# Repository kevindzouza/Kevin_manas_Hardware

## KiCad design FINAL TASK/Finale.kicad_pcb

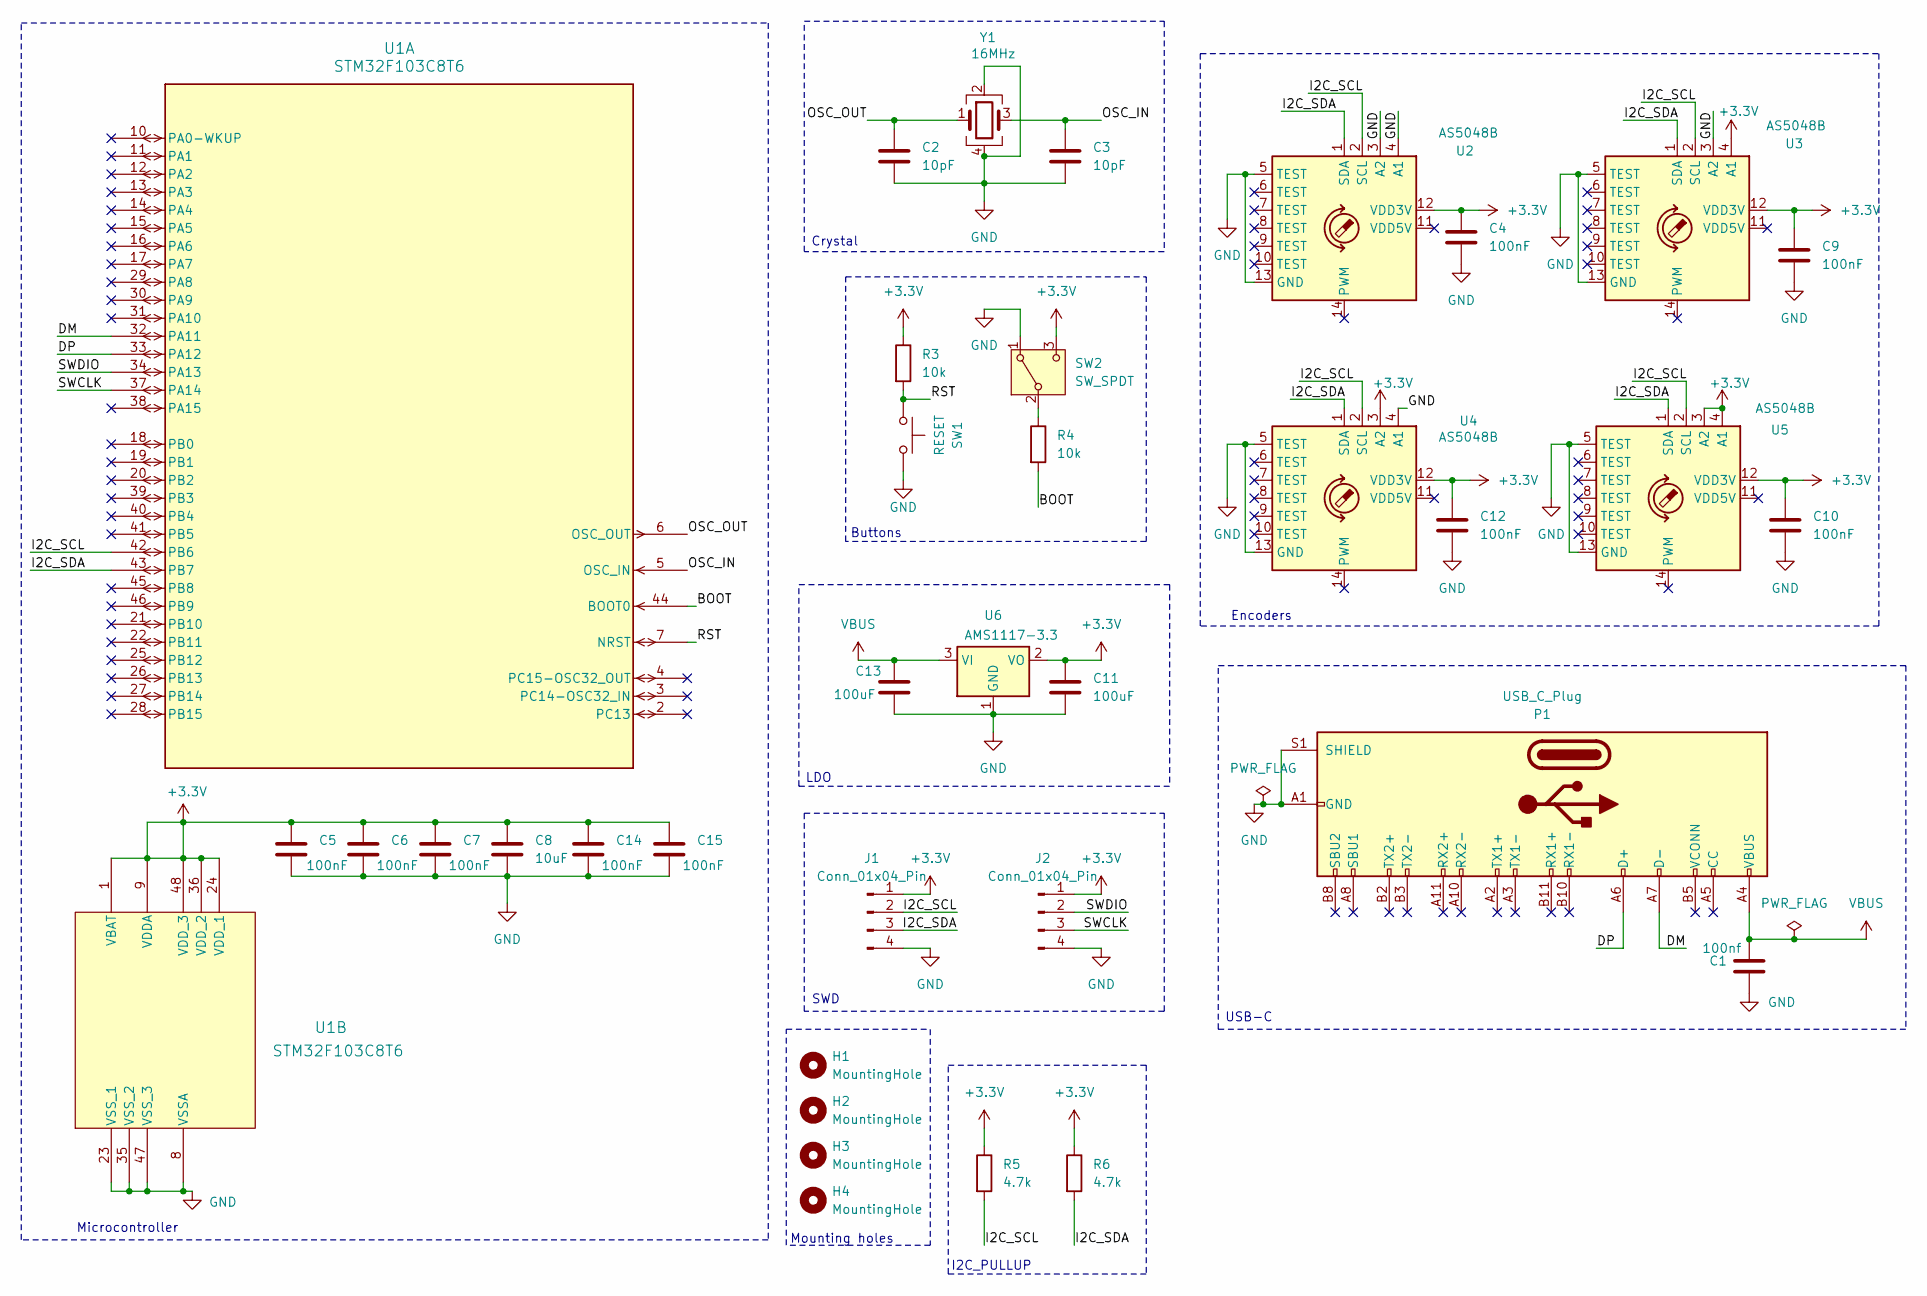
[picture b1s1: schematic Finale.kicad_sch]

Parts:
C1: 100nf; C_0805_2012Metric
C2, C3: 10pF; C_0402_1005Metric
C4, C5, C6, C7, C9, C10, C12, C14, C15: 100nF; C_0402_1005Metric
C8: 10uF; C_0805_2012Metric
C11, C13: 100uF; C_0402_1005Metric
H1, H2, H3, H4: MountingHole; MountingHole_2.1mm
J1, J2: Conn_01x04_Pin; JST_VH_B4P-VH-FB-B_1x04_P3.96mm_Vertical
P1: USB_C_Plug; GCT_USB4085-GF-A_REVB
R3, R4: 10k; R_0805_2012Metric
R5, R6: 4.7k; R_0805_2012Metric
SW1: RESET; SW_FSM8JH
SW2: SW_SPDT; SW_MINI-SPDT-SW
U1: STM32F103C8T6; LQFP48_STM
U2, U3, U4, U5: AS5048B; TSSOP-14_4.4x5mm_P0.65mm
U6: AMS1117-3.3; SOT-223-3_TabPin2
Y1: 16MHz; Crystal_SMD_3225-4Pin_3.2x2.5mm

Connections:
+3.3V: C4.1, C5.1, C6.1, C7.1, C8.1, C9.1, C10.1, C11.1, C12.1, C14.1, C15.1, J1.1, J2.1, R3.1, R5.1, R6.1, SW2.3 (C), U1.1 (VBAT), U1.9 (VDDA), U1.24 (VDD_1), U1.36 (VDD_2), U1.48 (VDD_3), U2.12 (VDD3V), U3.4 (A1), U3.12 (VDD3V), U4.3 (A2), U4.12 (VDD3V), U5.3 (A2), U5.4 (A1), U5.12 (VDD3V), U6.2 (VO)
/BOOT: R4.2, U1.44 (BOOT0)
/DM: P1.A7 (D-), U1.32 (PA11)
/DP: P1.A6 (D+), U1.33 (PA12)
/I2C_SCL: J1.2, R5.2, U1.42 (PB6), U2.2 (SCL), U3.2 (SCL), U4.2 (SCL), U5.2 (SCL)
/I2C_SDA: J1.3, R6.2, U1.43 (PB7), U2.1 (SDA), U3.1 (SDA), U4.1 (SDA), U5.1 (SDA)
/OSC_IN: C3.1, U1.5 (OSC_IN), Y1.3
/OSC_OUT: C2.1, U1.6 (OSC_OUT), Y1.1
/RST: R3.2, SW1.1, U1.7 (NRST)
/SWCLK: J2.3, U1.37 (PA14)
/SWDIO: J2.2, U1.34 (PA13)
GND: C1.1, C2.2, C3.2, C4.2, C5.2, C6.2, C7.2, C8.2, C9.2, C10.2, C11.2, C12.2, C13.2, C14.2, C15.2, J1.4, J2.4, P1.A1 (GND), P1.A12 (GND), P1.B1 (GND), P1.B12 (GND), P1.S1 (SHIELD), SW1.2, SW2.1 (A), U1.8 (VSSA), U1.23 (VSS_1), U1.35 (VSS_2), U1.47 (VSS_3), U2.3 (A2), U2.4 (A1), U2.5 (TEST), U2.13 (GND), U3.3 (A2), U3.5 (TEST), U3.13 (GND), U4.4 (A1), U4.5 (TEST), U4.13 (GND), U5.5 (TEST), U5.13 (GND), U6.1 (GND), Y1.2, Y1.4
unnamed: R4.1, SW2.2 (B)
VBUS: C1.2, C13.1, P1.A4 (VBUS), P1.A9 (VBUS), P1.B4 (VBUS), P1.B9 (VBUS), U6.3 (VI)

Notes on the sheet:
SWD
LDO
Encoders
USB-C
Microcontroller
Mounting holes
Buttons
I2C_PULLUP
Crystal

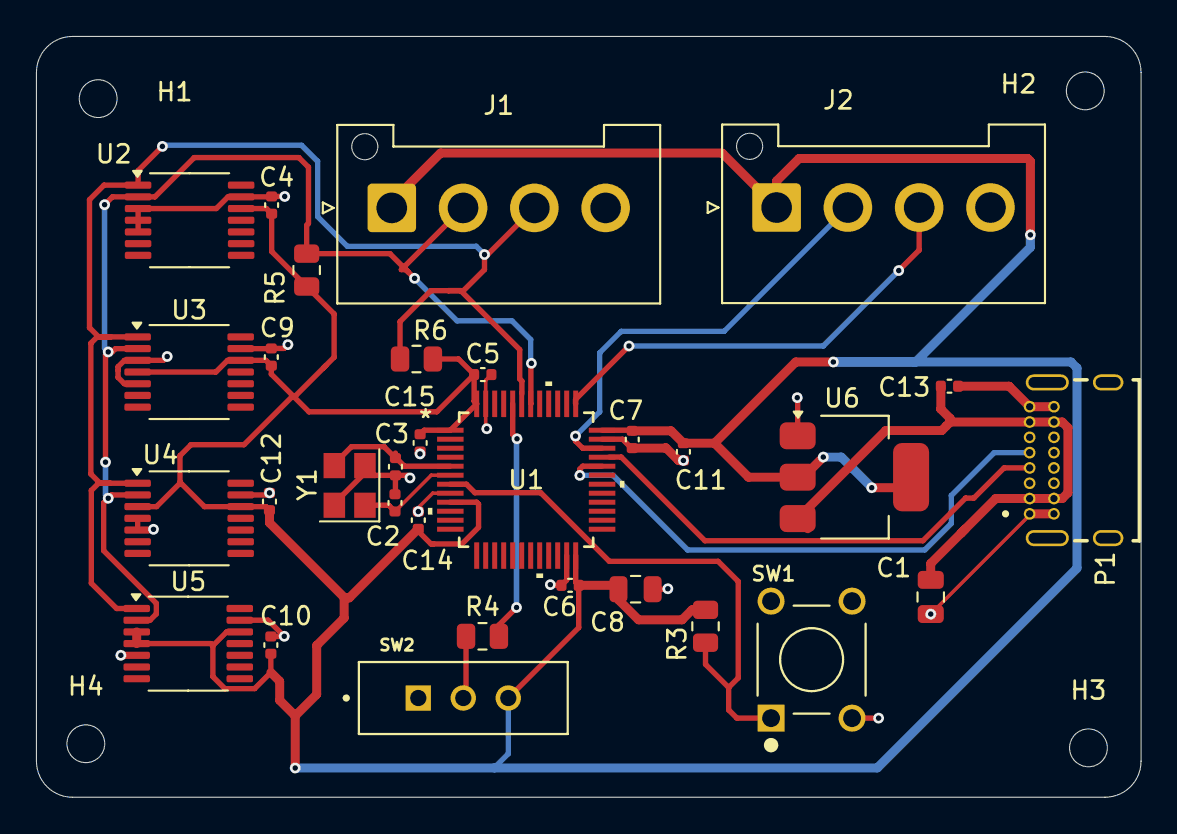
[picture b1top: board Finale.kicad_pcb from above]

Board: 2 copper layers, 61.4 x 42.3 mm, 35 parts (0 on the bottom side), 14 nets.

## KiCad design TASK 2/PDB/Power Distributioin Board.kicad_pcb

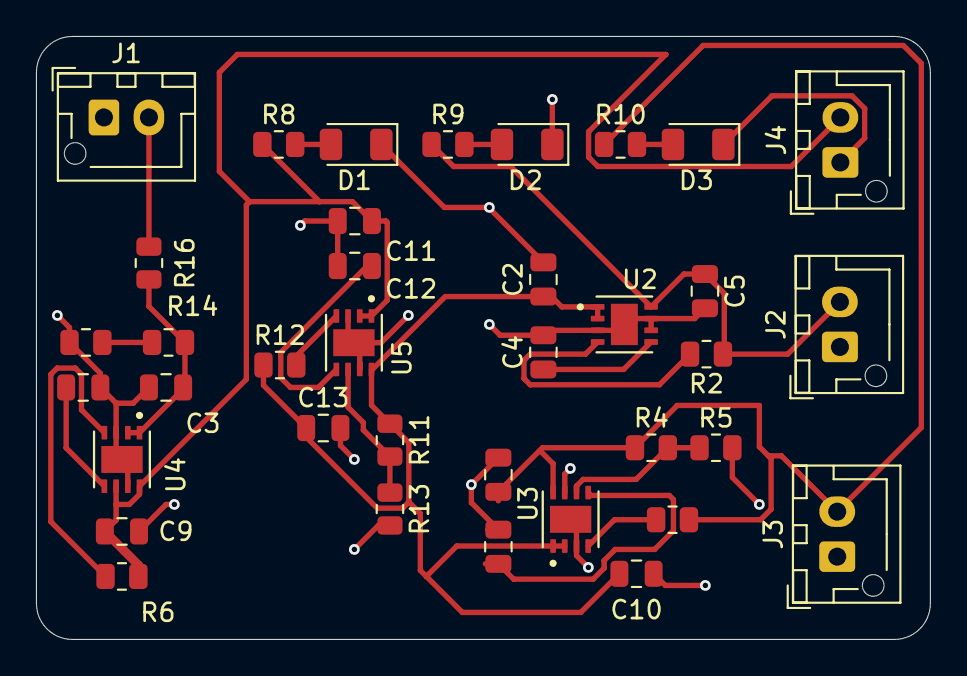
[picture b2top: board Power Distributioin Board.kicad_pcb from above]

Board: 2 copper layers, 49.7 x 33.5 mm, 37 parts (0 on the bottom side), 21 nets.

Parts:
C2, C10, C11: 1uF; C_0805_2012Metric
C3: 1.1uF; C_0805_2012Metric
C4, C6, C8, C12: 1nF; C_0805_2012Metric
C5, C7, C9, C13: 4.7uF; C_0805_2012Metric
D1, D2, D3: LED; LED_1206_3216Metric
J1: INPUT; JST_XH_B2B-XH-AM_1x02_P2.50mm_Vertical
J2: 3.3v; JST_XH_B2B-XH-AM_1x02_P2.50mm_Vertical
J3: 1.8v; JST_XH_B2B-XH-AM_1x02_P2.50mm_Vertical
J4: 5v; JST_XH_B2B-XH-AM_1x02_P2.50mm_Vertical
R2, R3, R5, R6, R12, R13: 10k; R_0805_2012Metric
R4: 4.3k; R_0805_2012Metric
R8, R9, R10: 1k; R_0805_2012Metric
R11: 22k; R_0805_2012Metric
R14, R15: 50k; R_0805_2012Metric
R16: 1; R_0805_2012Metric
U2, U3, U4, U5: MAX16910; SON65P300X300X80-9N

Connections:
/1.8v: C7.1, J3.2, R3.1, R4.1, R10.1, U3.8 (OUT)
/3.3v: C5.1, J2.2, R2.1, R9.1, U2.8 (OUT)
/5v: C9.1, C11.1, J4.2, R6.1, R8.1, U4.6 (SET0V), U4.8 (OUT), U5.1 (IN), U5.2 (ENABLE)
/INP: J1.2, R16.1
/inp: C2.1, C10.1, C13.1, R11.1, R12.1, U2.1 (IN), U2.2 (ENABLE), U3.1 (IN), U3.2 (ENABLE), U5.8 (OUT)
GND: C2.2, C3.2, C4.2, C5.2, C6.2, C7.2, C8.2, C9.2, C10.2, C11.2, C12.2, C13.2, D1.1 (K), D2.1 (K), D3.1 (K), J1.1, J2.1, J3.1, J4.1, R5.2, R13.2, R15.2, U2.3 (SET), U2.6 (SET0V), U2.7 (GND), U2.9 (GND/PAD), U3.3 (SET), U3.7 (GND), U3.9 (GND/PAD), U4.3 (SET), U4.7 (GND), U4.9 (GND/PAD), U5.3 (SET), U5.7 (GND), U5.9 (GND/PAD)
unnamed: D1.2 (A), R8.2
unnamed: D2.2 (A), R9.2
unnamed: D3.2 (A), R10.2
unnamed: C4.1, U2.5 (TIMEOUT)
unnamed: R2.2, U2.4 (~RST)
unnamed: R4.2, R5.1, U3.6 (SET0V)
unnamed: C6.1, U3.5 (TIMEOUT)
unnamed: R3.2, U3.4 (~RST)
unnamed: C3.1, R14.1, R16.2, U4.1 (IN), U4.2 (ENABLE)
unnamed: C8.1, U4.5 (TIMEOUT)
unnamed: R6.2, U4.4 (~RST)
unnamed: R11.2, R13.1, U5.6 (SET0V)
unnamed: C12.1, U5.5 (TIMEOUT)
unnamed: R12.2, U5.4 (~RST)
Vsense: R14.2, R15.1

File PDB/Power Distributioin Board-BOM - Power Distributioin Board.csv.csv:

Id,Designator,Footprint,Quantity,Designation,Amount
1,"R3,R12,R13,R6,R5,R2",R_0805_2012Metric,6,10k,302.76
2,"U5,U4,U2,U3",SON65P300X300X80-9N,4,MAX16910,1346.76
3,R11,R_0805_2012Metric,1,22k,40.89
4,"C13,C9,C7,C5",C_0805_2012Metric,4,4.7uF,40
5,"C12,C8,C4,C6",C_0805_2012Metric,4,1nF,64
6,"C11,C10,C2",C_0805_2012Metric,3,1uF,64
7,R16,R_0805_2012Metric,1,1,65.25
8,"R15,R14",R_0805_2012Metric,2,50k,24.36
9,"R10,R9,R8",R_0805_2012Metric,3,1k,224.46
10,J4,JST_XH_B2B-XH-AM_1x02_P2.50mm_Vertical,1,5v,7
11,J3,JST_XH_B2B-XH-AM_1x02_P2.50mm_Vertical,1,1.8v,7
12,J2,JST_XH_B2B-XH-AM_1x02_P2.50mm_Vertical,1,3.3v,7
13,J1,JST_XH_B2B-XH-AM_1x02_P2.50mm_Vertical,1,INPUT,7
14,"D3,D2,D1",LED_1206_3216Metric,3,LED,90
15,C3,C_0805_2012Metric,1,1.1uF,70.96
16,R4,R_0805_2012Metric,1,4.3k,30
,,,,Total -,2391.44

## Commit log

2025-03-25 Mux-2:1
2025-03-29 Added to a folder
2025-03-31 Added Pcb board file
2025-04-05 I2C commit -1
2025-04-08 Added UART communication
2025-04-13 Adc added
2025-04-20 Schematic pushed
2025-04-21 Added working directory
2025-04-23 Done
